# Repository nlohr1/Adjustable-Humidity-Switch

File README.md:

### Adjustable-Humidity-Switch

## EN: Adjustable Humidity-Switch
**Simple (de-)humidifier switch for all basements.**

Together with a dehumidifier or a mobile air conditioner, possibly with additional exhaust air, this is a way to keep out the poisonous "Aspergillus" (black or green mold) found in almost all basements, without using too much electricity. Unfortunately, with most dehumidifiers, the fan is always running - it cannot be switched off - and a ~800W to 3500W device can "eat up" a lot of electricity (150W continuous power for the fan?) - even if the compressor consumes most of it.  
What many people don't know or don't think about is that in many basements an invisible, radioactive gas diffuses out of the ground: radon. This gas is also odorless, so it is not noticeable, but acts like smoke - and in concentrations higher than the recommended limit (300 Bq/m³) it can attack the lungs in the long term... So if you are thinking of setting up a workspace or bedroom in the basement, you should also set up an appropriate extraction system.  
Another advantage of such an exhaust device compared to air conditioning systems or dehumidifiers: the moist, warm (+radon-containing) air is transported outside and the (indoor) air temperature remains almost the same without heating up (compressor waste heat).  
This switch works with a power relay, which can switch a consumer/device up to approx. 1400W on or off.  
The humidity threshold (the best for people is a relative humidity between 50-60%) - can be set with this switch. The dehumidifier is switched off with a small hysteresis (approx. -8% below the set value).  
I chose a capacitor type for the humidity sensor, the DHT22, because the DHT series is relatively stable and insensitive to environmental influences.  
I created and optimized the programming of the "Arduino Mini Pro" module, which handles the control and the LCD display, with the help of ChatGPT. This help makes troubleshooting in the program sequence much easier these days - so debugging is already extremely easyer.  
If you want to recreate the electronics required for this yourself, you can do it on a perforated board or recreate the board quite easily with the help of external service providers such as Eurocircuits or others. There are even (expensive) offers that take care of the assembly of the circuit board themselves. However, soldering in the few "THD" components should not be a problem for a DIY hobbyist.  

## DE: Einstellbarer Feuchte-Schalter
**Einfacher (Ent-)Feuchte Schalter für alle Keller.**

Zusammen mit einem Luftentfeuchter oder einem mobilen Klimagerät, evtl. mit zusätzlicher Abluft, ist dies eine Möglichkeit, den in fast allen Kellern anzutreffenden, giftigen "Aspergillus" (schwarzer oder grüner Schimmelbefall) fernzuhalten, ohne dabei allzu viel Strom zu verbrauchen. Bei den meisten Luftentfeuchtern läuft nämlich der Ventilator leider immer durch - nicht abschaltbar - und so ein ~800W bis 3500W Gerät kann tüchtig "Strom fressen" (150W Dauerleistung für den Lüfter?) - auch wenn der Kompressor das Meiste davon schluckt.  
Was viele zudem nicht wissen oder nicht daran denken - in vielen Kellern diffundiert ein unsichtbares, radioaktives Gas aus dem Boden: Radon. Dieses Gas ist zudem geruchlos, also nicht wahrnehmbar, wirkt aber wie Rauch - und kann in höherer Konzentration als dem empfohlenen Grenzwert (300 Bq/m³) längerfristig die Lunge angreifen... Falls man also gedenkt im Keller einen Arbeitsplatz oder ein Schlafzimmer einzurichten, sollte man dazu auch gleich eine entsprechende Absauganlage einrichten.  
Ein weiterer Vorteil eines solchen Abluft-Gerätes gegenüber Klimaanlagen oder Entfeuchtern: die feuchte, warme (+radonhaltige) Luft wird nach draußen befördert und die (Innen-)Lufttemperatur bleibt annähernd gleich, ohne sich zu erhitzen (Kompressor-Abwärme).  
Dieser Schalter arbeitet mit einem Power-Relais zusammen, welches einen Verbraucher/Gerät bis zu ca. 1400W ein- bzw. ausschalten kann.  
Die Feuchtigkeits-Schwelle (am besten für Menschen ist eine relative Luftfeuchtigkeit zwischen 50-60%) - ist bei diesem Schalter einstellbar. Mit einer kleinen Hysterese (ca. -8% unter dem eingestellten Wert) wird der Entfeuchter ausgestellt.  
Als Feuchtesensor habe ich einen Kondensator-Typ gewählt, den DHT22, da die DHT-Serie gegen Umwelteinflüsse relativ stabil und unempfindlich ist.  
Die Programmierung des "Arduino-Mini-Pro" Moduls, welches die Steuerung und die LCD-Anzeige übernimmt, habe ich mit Hilfe von ChatGPT erstellt und optimiert. Diese Hilfe vereinfacht heutzutage die Fehlersuche im Programmablauf - das "debugging" schon extrem.  
Wer die dazu erforderliche Elektronik selbst nachbauen will, kann diese auf einer Lochrasterplatine oder das Board mit Hilfe von externen Dienstleistern wie Eurocircuits o.a. auf recht einfache Weise nachbauen. Es gibt dazu sogar (teure) Angebote, die selbst die Bestückung der Leiterplatte übernhemen. Die wenigen "THD"-Bauteile einzulöten sollte aber kein Problem für einen DIY-Bastler sein.

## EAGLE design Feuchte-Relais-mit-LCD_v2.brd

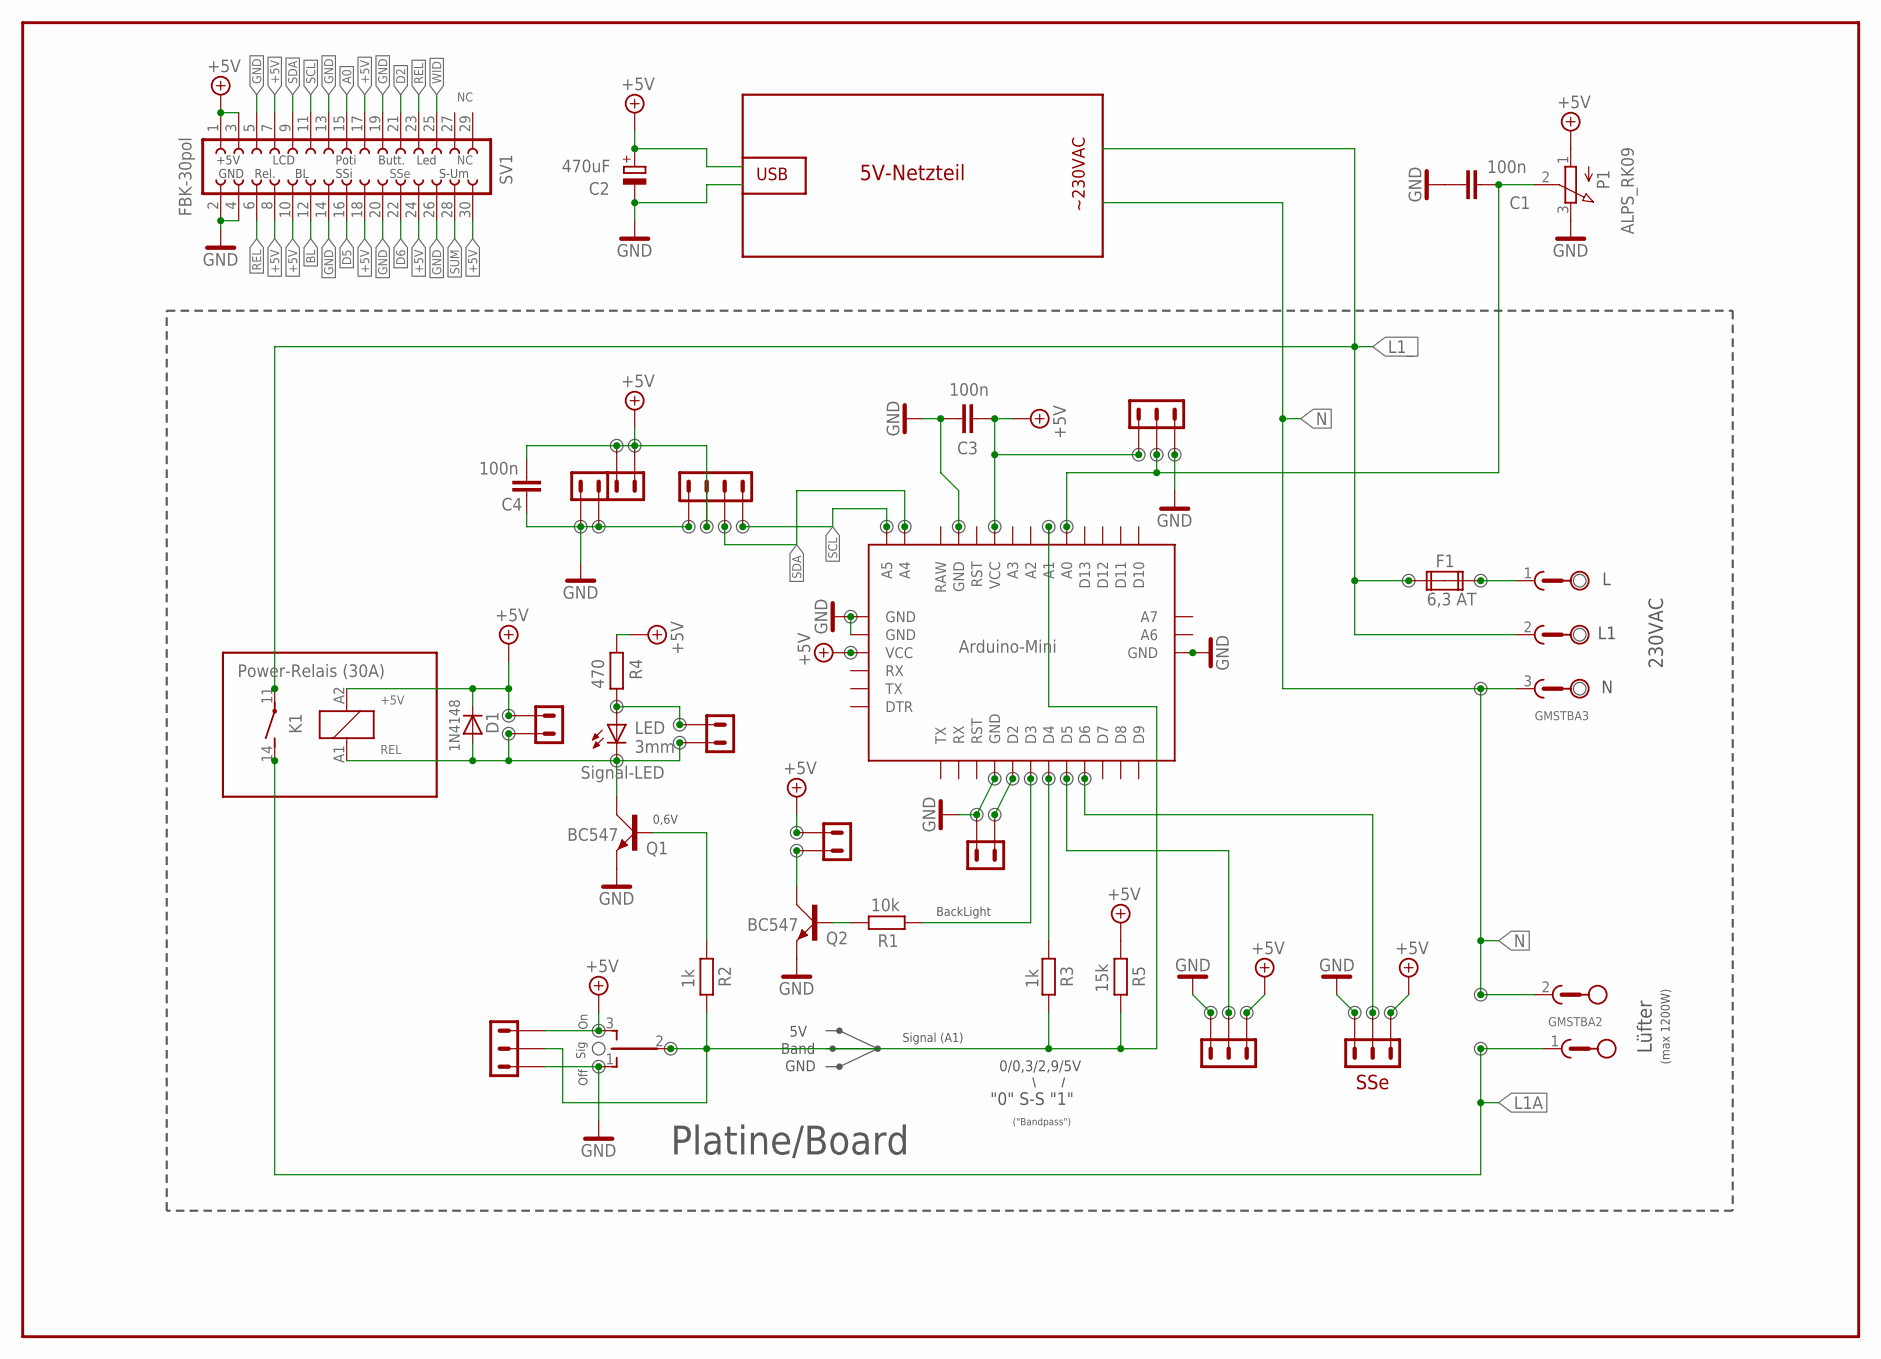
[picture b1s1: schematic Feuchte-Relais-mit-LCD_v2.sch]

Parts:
230VAC: GMSTBA3
BOARD: Arduino-Mini; ARDU-MINI
C1, C3, C4: 100n; C025-024X044
C2: 470uF; E3,5-8
D1: 1N4148; D-2.5
F1: 6,3 AT; FUSE1
K1: Power-Relais (30A); ZD2
LED1: o3mm; LED3MM
LüFTER: GMSTBA2
P1: ALPS_RK09; RK09
Q1, Q2: BC547; SOT54A
R1: 10k; 0204/7
R2, R3: 1k; 0204V
R4: 470; 0204V
R5: 15k; 0204V
SUM: TL39PO; TL3XPO
SV1: FBK-30pol; FE15-2

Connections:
+5V: BOARD.P$21 (VCC), BOARD.P$27 (VCC), C2.+, C3.1, C4.2, D1.C, K1.A2 (2), P1.1 (A), R4.1, R5.1, SUM.3 (S), SV1.1, SV1.3, SV1.7, SV1.8, SV1.10, SV1.17, SV1.18, SV1.24, SV1.30
A0: BOARD.P$17 (A0), C1.2, P1.2 (S), SV1.15
A1: BOARD.P$18 (A1), R2.1, R3.2, R5.2, SUM.2
BL: Q2.C, SV1.12
D2: BOARD.P$5 (D2), SV1.21
D3: BOARD.P$6 (D3), R1.1
D4: BOARD.P$7 (D4), R3.1
D5: BOARD.P$8 (D5), SV1.16
D6: BOARD.P$9 (D6), SV1.22
GND: BOARD.P$4 (GND), BOARD.P$23 (GND), BOARD.P$25 (GND), BOARD.P$26 (GND), BOARD.P$31 (GND), C1.1, C2.-, C3.2, C4.1, P1.3 (E), Q1.E, Q2.E, SUM.1 (O), SV1.2, SV1.4, SV1.5, SV1.13, SV1.14, SV1.19, SV1.20, SV1.26
L: 230VAC.1, F1.2A
L1A: K1.14 (S), LüFTER.1
L1_: 230VAC.2, F1.1A, K1.11
N: 230VAC.3, LüFTER.2
unnamed: Q1.B, R2.2
unnamed: Q2.B, R1.2
REL: D1.A, K1.A1 (1), LED1.K (C), Q1.C, SV1.6, SV1.23
SCL: BOARD.P$35 (A5), SV1.11
SDA: BOARD.P$34 (A4), SV1.9
SUM: SV1.28
WID: LED1.A, R4.2, SV1.25

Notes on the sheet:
USB
~230VAC
5V-Netzteil
Lüfter
Platine/Board
Off
Sig
Signal (A1)
230VAC
LED 3mm
BackLight
REL
+5V
(max 1200W)
Signal-LED
0/0,3/2,9/5V
"0" S-S "1"
("Bandpass")
0,6V
5V Band GND
GND
Rel.
LCD
S-Um
Butt.
Led
SSi
SSe
Poti

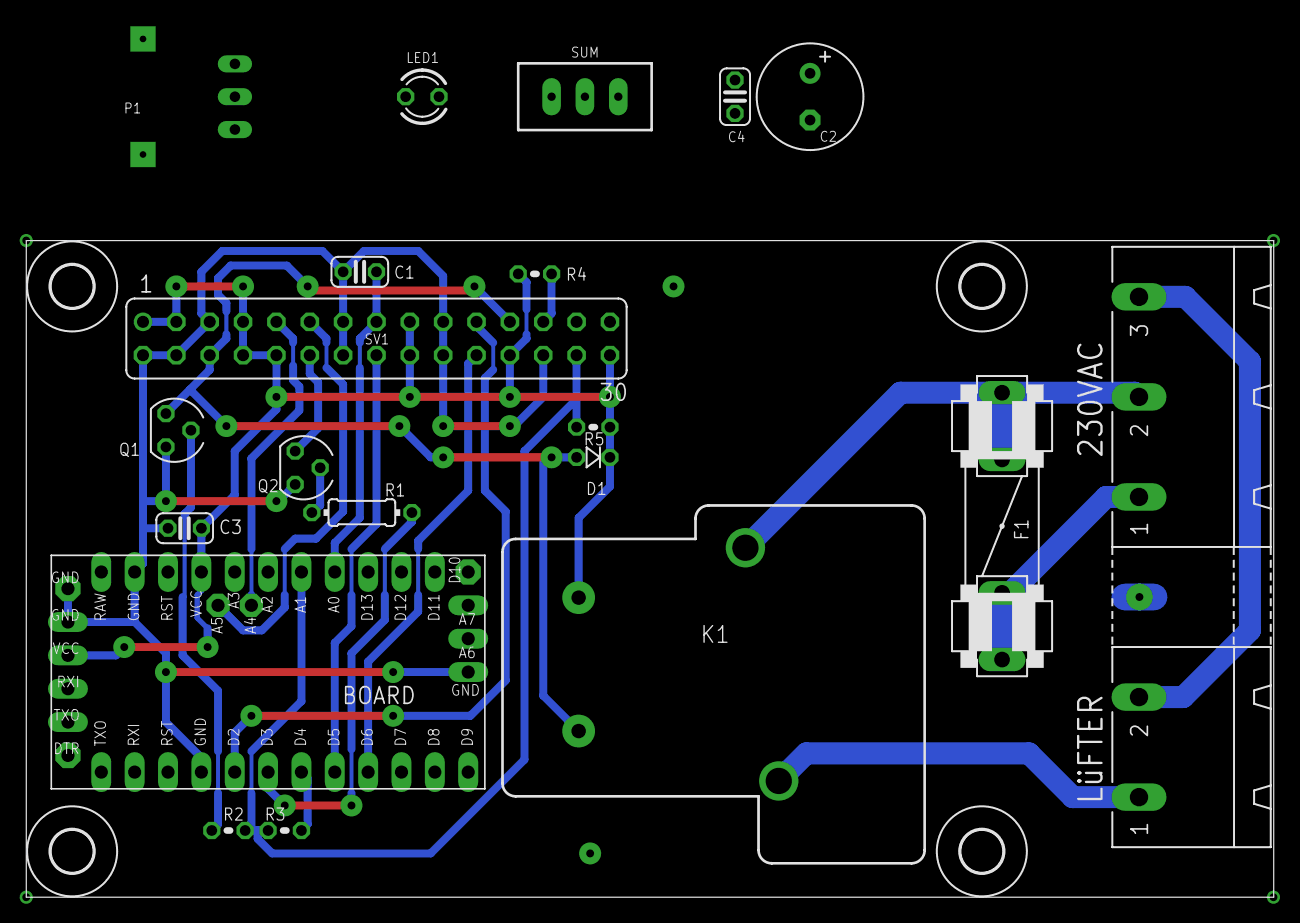
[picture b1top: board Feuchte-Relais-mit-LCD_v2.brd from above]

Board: 2 copper layers, 95.0 x 50.0 mm, 25 parts (1 on the bottom side), 20 nets.

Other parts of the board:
U$1, U$2, U$3, U$4: 3,2
